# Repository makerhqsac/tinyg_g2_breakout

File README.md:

# TinyG G2 Breakout Board

This board connects on top of an Arduino Due and then a grblshield is connected on top of this shield. This provides a TinyG G2 CNC control board with all the common pins for limit/homing switches and control pendant functionality to be easily connected to the Arduino Due.

Order from OSHPark [Here](https://oshpark.com/shared_projects/RuvmX1Bc)

[Schematic](https://github.com/makerhqsac/tinyg_g2_breakout/raw/master/tinyg_g2_breakout.pdf)

This is part of an overall TinyG G2 CNC control system. 3D printable files for the enclosure, control pendant and junction box can be
found here:

* Electronics Enclosure: http://www.thingiverse.com/thing:1703914
* Control Pendant: http://www.thingiverse.com/thing:1703922
* Junction Box: http://www.thingiverse.com/thing:1703927

Board in action:

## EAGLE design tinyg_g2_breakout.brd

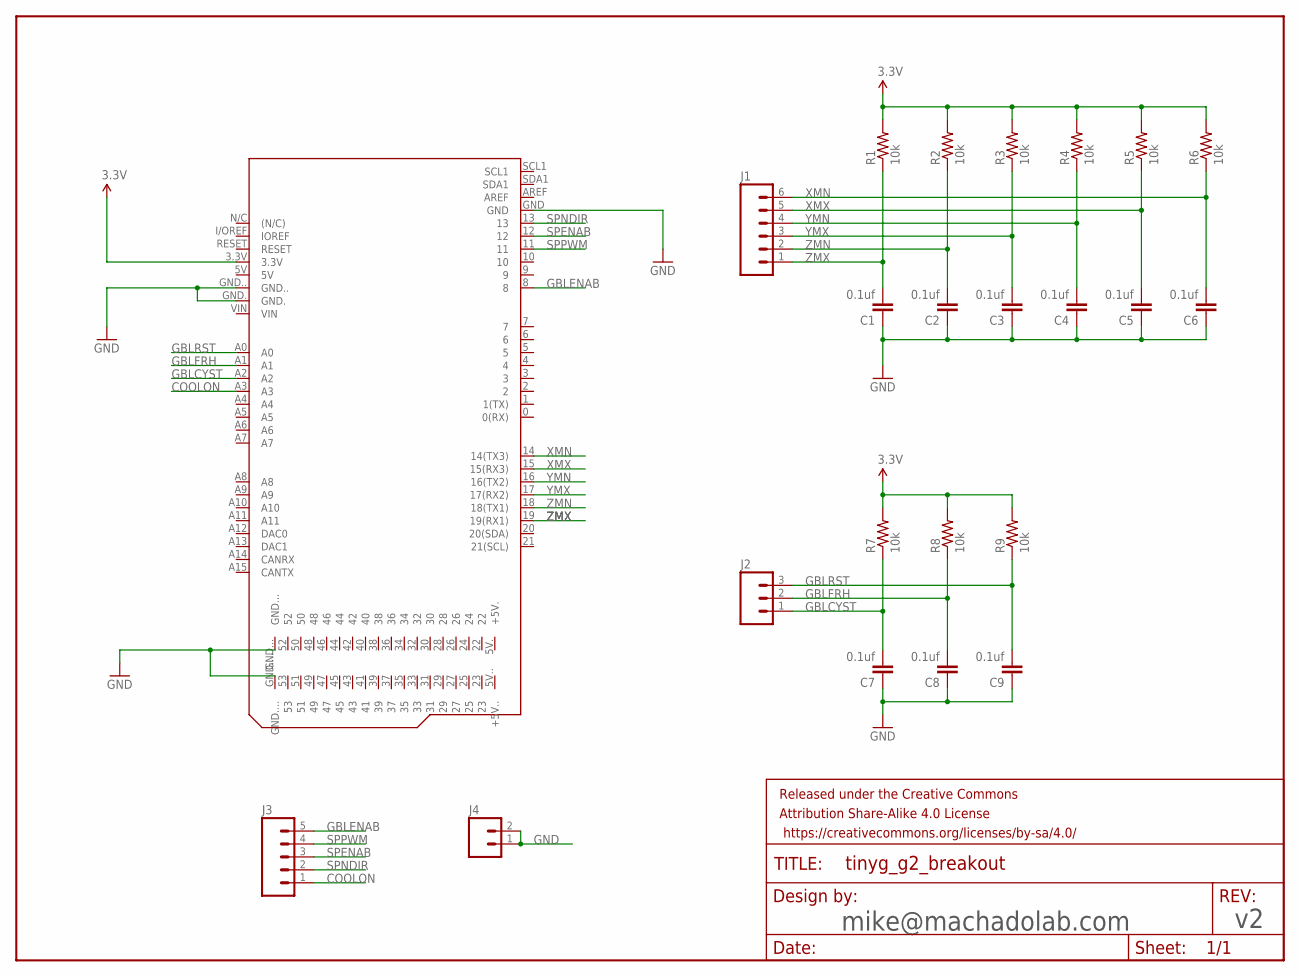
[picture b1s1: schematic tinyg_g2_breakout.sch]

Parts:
C1, C2, C3, C4, C5, C6, C7, C8, C9: 0.1uf; CAP-PTH-SMALL
FRAME1: v1; CREATIVE_COMMONS
J1: M06SILK_FEMALE_PTH; 1X06
J2: M03PTH; 1X03
J3: M05PTH; 1X05
J4: M02PTH; 1X02
PCB1: ARDUINO_DUE_SHIELD
R1, R2, R3, R4, R5, R6, R7, R8, R9: 10k; AXIAL-0.3

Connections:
3.3V: PCB1.3.3V, R1.P$2 (2), R2.P$2 (2), R3.P$2 (2), R4.P$2 (2), R5.P$2 (2), R6.P$2 (2), R7.P$2 (2), R8.P$2 (2), R9.P$2 (2)
COOLON: J3.1, PCB1.A3
GBLCYST: C7.2, J2.1, PCB1.A2, R7.P$1 (1)
GBLENAB: J3.5, PCB1.8
GBLFRH: C8.2, J2.2, PCB1.A1, R8.P$1 (1)
GBLRST: C9.2, J2.3, PCB1.A0, R9.P$1 (1)
GND: C1.1, C2.1, C3.1, C4.1, C5.1, C6.1, C7.1, C8.1, C9.1, J4.1, J4.2, PCB1.GND, PCB1.GND., PCB1.GND.., PCB1.GND..., PCB1.GND....
SPENAB: J3.3, PCB1.12
SPNDIR: J3.2, PCB1.13
SPPWM: J3.4, PCB1.11
XMN: C6.2, J1.6, PCB1.14 (14(TX3)), R6.P$1 (1)
XMX: C5.2, J1.5, PCB1.15 (15(RX3)), R5.P$1 (1)
YMN: C4.2, J1.4, PCB1.16 (16(TX2)), R4.P$1 (1)
YMX: C3.2, J1.3, PCB1.17 (17(RX2)), R3.P$1 (1)
ZMN: C2.2, J1.2, PCB1.18 (18(TX1)), R2.P$1 (1)
ZMX: C1.2, J1.1, PCB1.19 (19(RX1)), R1.P$1 (1)

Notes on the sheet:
mike@machadolab.com

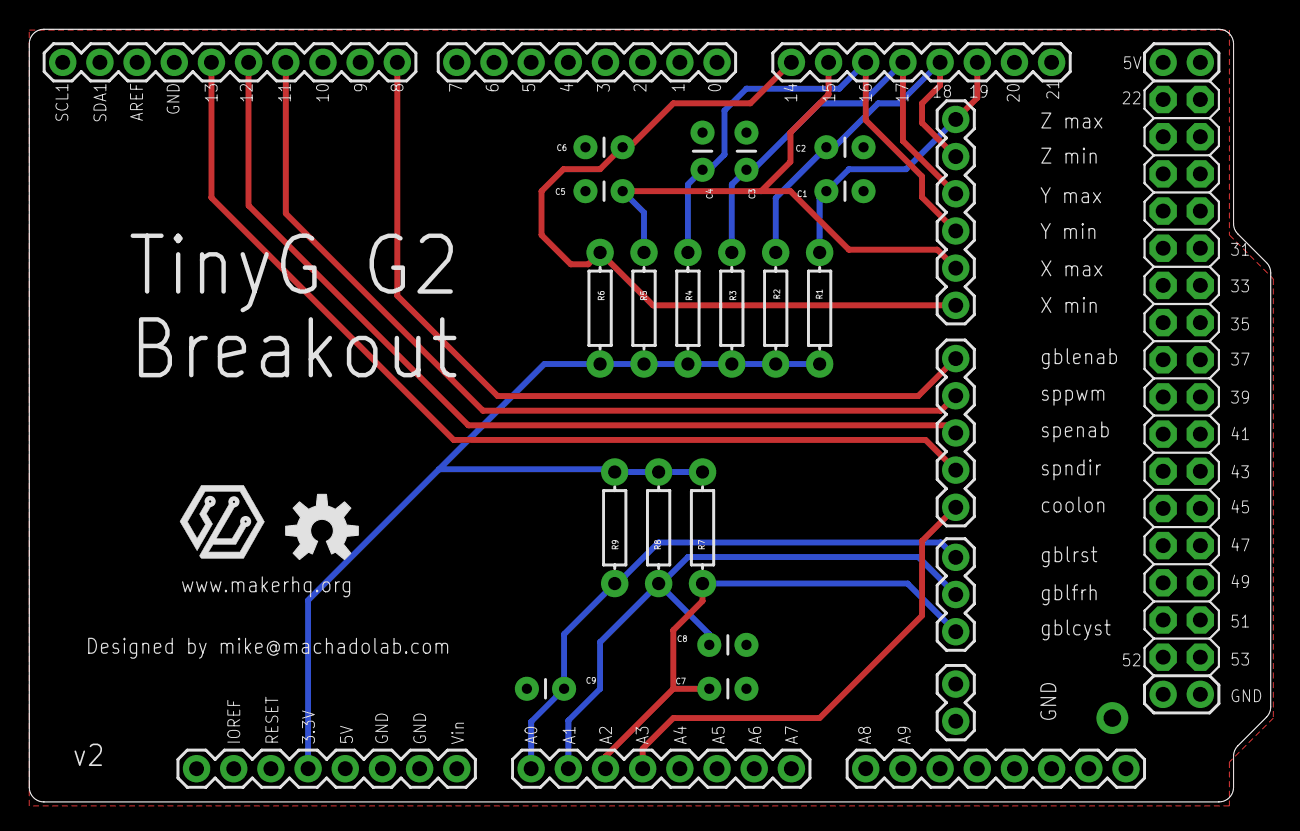
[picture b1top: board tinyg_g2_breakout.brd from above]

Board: 2 copper layers, 84.8 x 52.8 mm, 26 parts (0 on the bottom side), 16 nets.

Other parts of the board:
U$1: OSHW-LOGO-M
U$2: MAKERHQ_LOGO_L

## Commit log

2016-06-15 Initial import
2016-06-19 latest changes
2016-08-04 Updated files

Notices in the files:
parts and their libraries:
SparkFun-Connectors: Licensing: Creative Commons ShareAlike 4.0 International - https://creativecommons.org/licenses/by-sa/4.0
SparkFun-Aesthetics: Released under the Creative Commons Attribution Share-Alike 4.0 License
SparkFun-Aesthetics: https://creativecommons.org/licenses/by-sa/4.0
